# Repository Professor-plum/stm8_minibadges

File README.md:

# stm8_minibadges
Repository of mini badges using the stm8s001j3.

This repo contains all the source code and eagle files for the mini badges I've designed using the STM8S001J3 microprocessor. I've loved this little chip as it's cheaper than an ATTiny and extremely versatile. The package design leaves a bit to be desired as it wastes one pin for a required cap and the pin 1 marking is horrible but for $.23 you can't complain much.

## Assembly

I'd recommend soldering the LCD down first, followed by the STM8 chip (note the orientation) then the resistor and capacitor. Finally, solder on the pin header legs once all the surface mount components are down. 

## Flashing

In all my stm8 projects I do bare metal programming and utilize no libraries (I'm usually wanting to make the most of that 8K flash)

There’s also a lot of code reuse between these projects. I could probably do better at managing that, meh...

The following tools are required to compile and flash the chips:
* [ST-Link V2](http://www.ebay.com/sch/i.html?_from=R40&_trksid=p2050601.m570.l1313.TR0.TRC0.H0.Xstlink+v2.TRS0&_nkw=stlink+v2&_sacat=0)
* [sdcc](https://sourceforge.net/projects/sdcc/files/snapshot_builds/)
* [stm8flash](https://github.com/vdudouyt/stm8flash)

To flash the badge there are only three that need to be connected from the ST-Link to the minibadge. 
* That is 3V3 to the lower 3V
* GND to ether GND
* SWIM to NC12 (4th pin from the right on the bottom row)

Usually, the process for compiling and flashing is the same for all projects. That is:

```bash
>sdcc -lstm8 -mstm8 --out-fmt-ihx main.c
>stm8flash -c stlinkv2 -p stm8s001j3 -w main.ihx
```

The stm8flash command usually needs to be executed twice, the first rarely takes.
A successful flash outputs something similar to this

```
Determine FLASH area
Due to its file extension (or lack thereof), "main.ihx" is considered as INTEL HEX format!
4456 bytes at 0x8000... OK
Bytes written: 4456
```

I apologize for the lack of code comments but I don’t really care enough to do something about it :/

The colors may be inverted depending on the TFT LCD type you have. The simple fix is to locate the line `ST7735_Write(ST7735_INVOFF, CMD);` in the main.c file and change it to `ST7735_Write(ST7735_INVON, CMD);` or vice versa. Then recompile and reflash.

The official documentation for this chip can be found at https://www.st.com/resource/en/datasheet/stm8s001j3.pdf

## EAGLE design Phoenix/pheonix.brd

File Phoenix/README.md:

# Phoenix mini badge

This badge had a CTF associated with it. The badge face is touch sensitive and would display a URL on the main badge when touched. There were some issues with the 2019 SAINTCON badge and the link would display in like 1:100 touches.

The eye slowly pulses normally and blinks rapidly when touched

## Bill of Materials
* STM8S001J3
* LS T77K-K1 Red LED
* 470 Ohm 1206 Resistor
* 1M Ohm 1206 Resistor
* 1uF 1206 Capacitor
* pin headers

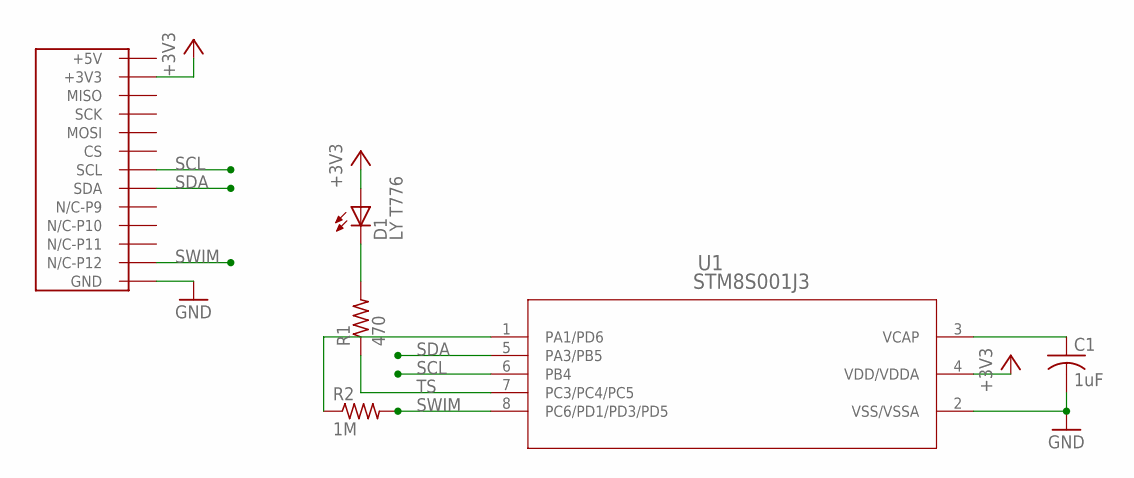
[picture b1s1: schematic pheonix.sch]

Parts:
C1: 1uF; C1206
D1: LY T776; P-LCC-2-TOPLED-RG-SMALL
R1: 470; M1206
R2: 1M; M1206
U1: STM8S001J3; SOD8N_4P9X6
U$1: BADGE64FOOTPRINT; BADGE64-FOOTPRINT

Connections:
+3V3: D1.A, U1.4 (VDD/VDDA), U$1.+3V3-P7 (+3V3), U$1.+3V3-P15 (+3V3)
+5V: U$1.+5V
GND: C1.2, U1.2 (VSS/VSSA), U$1.GND-P2 (GND), U$1.GND-P8 (GND), U$1.GND-P16 (GND)
unnamed: D1.C, R1.2
unnamed: R1.1, U1.7 (PC3/PC4/PC5)
unnamed: C1.1, U1.3 (VCAP)
SCL: U1.6 (PB4), U$1.SCL
SDA: U1.5 (PA3/PB5), U$1.SDA
SWIM: R2.2, U1.8 (PC6/PD1/PD3/PD5), U$1.NC-P12 (N/C-P12)
TS: R2.1, U1.1 (PA1/PD6)

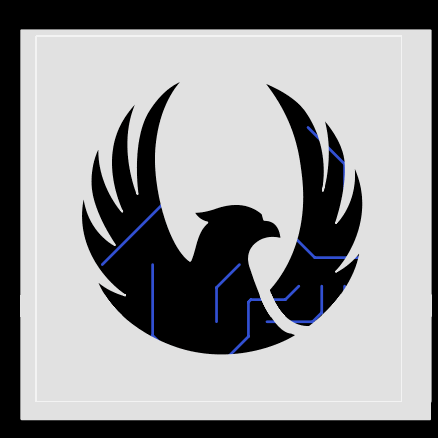
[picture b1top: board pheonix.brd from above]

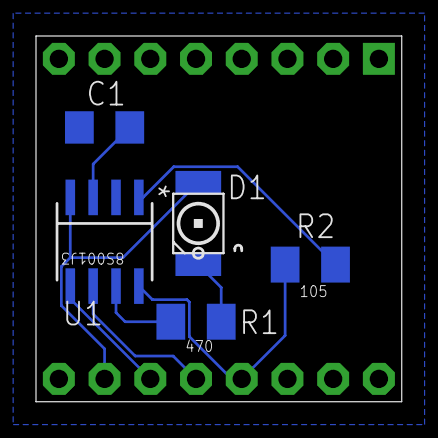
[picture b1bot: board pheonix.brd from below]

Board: 2 copper layers, 20.3 x 20.3 mm, 6 parts (5 on the bottom side), 9 nets.

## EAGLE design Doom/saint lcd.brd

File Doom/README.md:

# Doom Mini Badge!

## Bill of Materials 
* 0.96" 80x160 ST7735 TFT LCD Display
* STMS001J3
* 22 Ohm 0603 Resistor
* 1uF 0603 Capacitor
* Pin headers

Same hardware as the Metroid Mini Badge

Doom face from orignal game. Shows random expression (always full health)

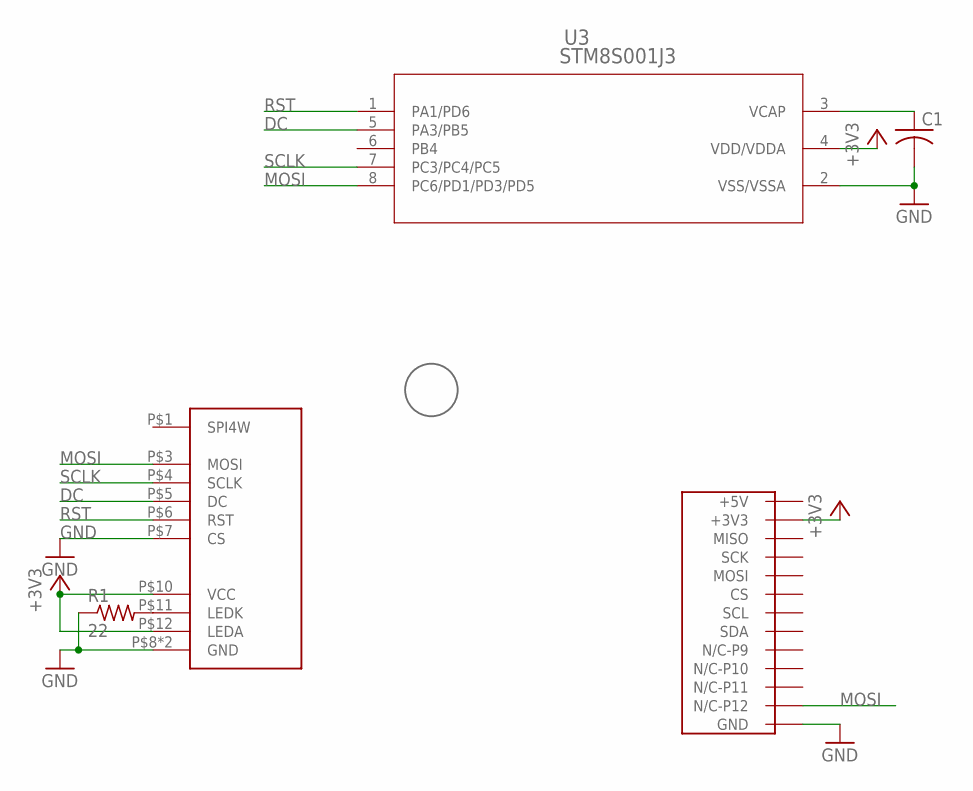
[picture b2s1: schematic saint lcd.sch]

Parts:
C1: C-USC0603; C0603
R1: 22; R0603
U3: STM8S001J3; SOD8N_4P9X6
U$1: BADGE64FOOTPRINT; BADGE64-FOOTPRINT
U$2: FPC13
U$3: PLUM

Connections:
+3V3: U3.4 (VDD/VDDA), U$1.+3V3-P7 (+3V3), U$1.+3V3-P15 (+3V3), U$2.P$10 (VCC), U$2.P$12 (LEDA)
+5V: U$1.+5V
DC: U3.5 (PA3/PB5), U$2.P$5 (DC)
GND: C1.2, R1.1, U3.2 (VSS/VSSA), U$1.GND-P2 (GND), U$1.GND-P8 (GND), U$1.GND-P16 (GND), U$2.P$7 (CS), U$2.P$8 (GND), U$2.P$13 (GND)
MOSI: U3.8 (PC6/PD1/PD3/PD5), U$1.NC-P12 (N/C-P12), U$2.P$3 (MOSI)
unnamed: R1.2, U$2.P$11 (LEDK)
unnamed: C1.1, U3.3 (VCAP)
RST: U3.1 (PA1/PD6), U$2.P$6 (RST)
SCLK: U3.7 (PC3/PC4/PC5), U$2.P$4 (SCLK)

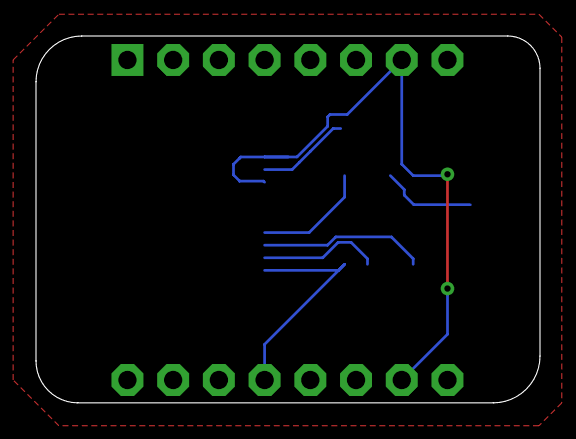
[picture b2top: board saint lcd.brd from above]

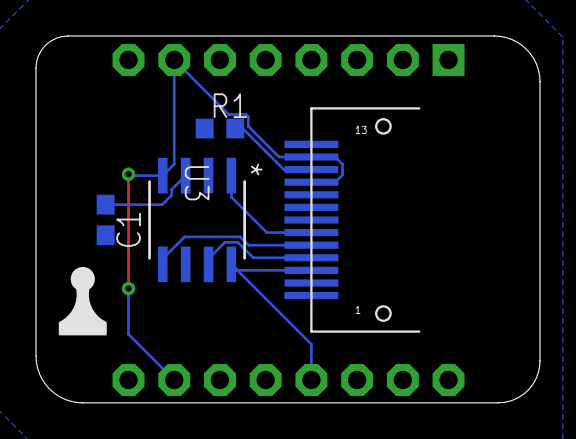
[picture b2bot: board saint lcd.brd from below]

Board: 2 copper layers, 28.0 x 20.4 mm, 6 parts (5 on the bottom side), 8 nets.

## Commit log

2019-10-25 Update README.md
    Readme added
2019-10-25 Added content
2019-10-25 Metroid Readme
2019-10-25 Added metroid sprites
2019-10-25 shrinking gif
2021-10-20 Added pitfall code
2021-10-20 Typos
2021-10-20 clean up
2023-08-12 Added Doom guy firmware
2023-08-29 Add doom.gif
2023-08-29 Add layout image
2023-10-29 Added improvments to allow reflashing

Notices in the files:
parts and their libraries:
MiniBadge: Licensing: Creative Commons ShareAlike 4.0 International - https://creativecommons.org/licenses/by-sa/4.0
